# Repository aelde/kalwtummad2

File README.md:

# kalwtummad2
# mini robot

**car robot control over wifi / control over hand using mqtt**\
3d : <https://collaborate.shapr3d.com/v/xkKrqxI_4FUdMemtdK0US>

โปรเจคนี้เกิดจากความสนใจใน esp32 ของผมและพอดีช่วงนั้นอาจารย์มีหุ่นยนต์ดูดฝุ่นราคาถูกที่ไม่ได้ใช้อยู่ตัวนึง และพอดีกับที่ผมมี mpu6050 อยู่ที่บ้านพอดี ผมเลยเกิดไอเดียที่จะสร้างหุ่นยนต์ที่บังคับด้วยการขยับของมือขึ้นมา
เริ่มจากการที่แกะชิ้นส่วนทั้งหมดออกแล้วก็เอาอุปกรณ์ใหม่ใส่เข้าไปแทนหมด แล้วจากนั้นก็เชื่อมอุปกรณ์ทั้งหมดกับ esp32 จนเกิดเป็นหุ่นย์นี้ขึ้นมา(kalwtummad) โดยหุ่นย์นี้จะบังคับด้วยมือผ่าน mqtt และยังสามารถบังคับผ่านหน้า dashboard ได้ด้วย

อุปกรณ์หลักๆใน project
  - esp32
  - mpu6050
  - l298n
  - lcd1602
  - I2C liquid crystal displays

การใช้งาน : หมุนมือไปในทิศที่ต้องการจะให้รถวิ่ง ดูใน HOW_TO_USE.jpeg

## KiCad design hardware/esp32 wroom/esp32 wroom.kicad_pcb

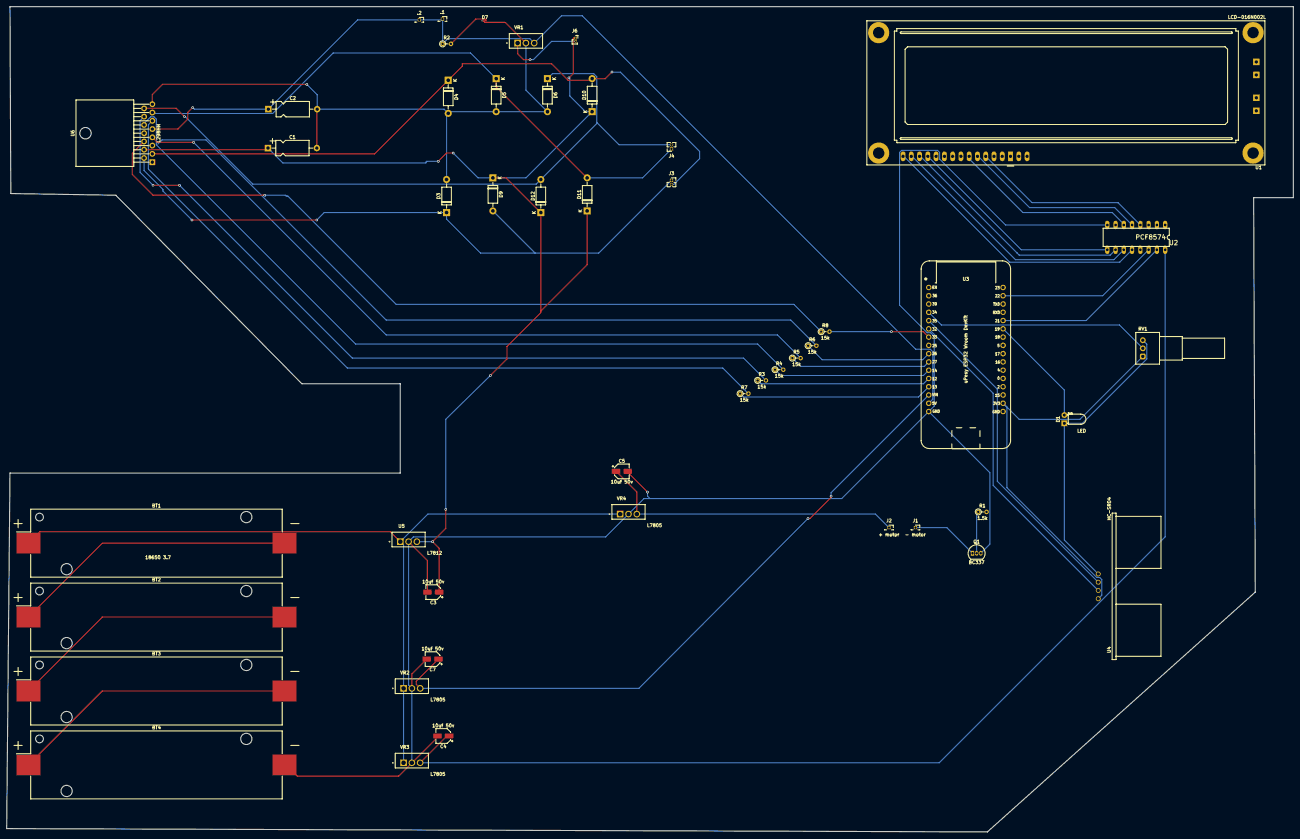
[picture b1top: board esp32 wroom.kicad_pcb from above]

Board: 2 copper layers, 395.2 x 253.5 mm, 47 parts (0 on the bottom side), 47 nets.

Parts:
.1, .2: PinSocket_1x01_P1.27mm_Vertical
BT1, BT2, BT3, BT4: 18650 3.7; BatteryHolder_Keystone_1042_1x18650
C1, C2: 220uf; CP_Axial_L10.0mm_D4.5mm_P15.00mm_Horizontal
C3, C4, C5, C7: 10uf 50v; CP_Elec_4x3.9
D1: LED; LED_D3.0mm_Horizontal_O1.27mm_Z2.0mm
D3, D4, D5, D6, D9, D10, D11, D12: 1N4007; D_DO-41_SOD81_P10.16mm_Horizontal
D7: LED; LED_0201_0603Metric
J1: - motor; PinSocket_1x01_P1.27mm_Vertical
J2: + motor; PinSocket_1x01_P1.27mm_Vertical
J3: motorA; PinSocket_1x02_P1.27mm_Vertical
J4: motorB; PinSocket_1x02_P1.27mm_Vertical
J6: PinSocket_1x02_P1.00mm_Vertical
Q1: BC337; TO-92_Inline
R1: 1.5k; R_Axial_DIN0204_L3.6mm_D1.6mm_P2.54mm_Vertical
R2: 1k; R_Axial_DIN0204_L3.6mm_D1.6mm_P2.54mm_Vertical
R3, R4, R5, R6, R7, R8: 15k; R_Axial_DIN0204_L3.6mm_D1.6mm_P2.54mm_Vertical
RV1: R_Potentiometer; Potentiometer_Alps_RK097_Single_Horizontal
U1: LCD-016N002L
U2: PCF8574; DIL16
U3: uPesy_ESP32_Wroom_DevKit
U4: HC-SR04
U5: L7812; L7805
U6: L298HN; TO-220-15_P2.54x2.54mm_StaggerOdd_Lead5.84mm_TabDown
VR1, VR2, VR3, VR4: L7805

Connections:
5v: .1.1, .2.1, C2.1, R2.1, U3.15 (5V), U6.9 (Vss), VR1.3 (OUTPUT)
/3v3: RV1.1, U3.31 (3V3), U4.1 (VCC)
/5v_control: C7.1, U3.14 (VIN), VR2.3 (OUTPUT)
/5v_lcd: C4.1, U2.16 (VDD), VR3.3 (OUTPUT)
/12v_wheel: C1.1, C3.1, D9.1 (K), D10.1 (K), D11.1 (K), D12.1 (K), J6.1, U5.3 (OUT), U6.4 (Vs)
/D12: R3.1, U3.12 (GPIO12)
/D14: R4.1, U3.11 (GPIO14)
/D18: R1.2, U3.23 (GPIO18)
/D19: D1.2 (A), U3.22 (GPIO19)
/D21: U2.15 (SDA), U3.21 (GPIO21)
/D22: U2.14 (SCL), U3.18 (GPIO22)
/D25: R7.1, U3.13 (GPIO13)
/D26: R6.1, U3.9 (GPIO26)
/D27: R5.1, U3.10 (GPIO27)
/D32: U3.6 (GPIO32), U4.2 (TRIG)
/D33: R8.2, U3.7 (GPIO33)
/D34: RV1.2, U3.4 (GPIO34)
/D35: U3.5 (GPIO35), U4.3 (ECHO)
/GND_1: D1.1 (K), RV1.3, U3.32 (GND), U4.4 (GND)
/dust motor: C5.1, J2.1, VR4.3 (OUTPUT)
Earth: C1.2, C2.2, D3.2 (A), D4.2 (A), D5.2 (A), D6.2 (A), D7.1 (K), U6.1 (SENSE_A), U6.8 (GND), U6.15 (SENSE_B), VR1.2 (GROUND)
GND: BT4.2 (-), C3.2, C4.2, C5.2, C7.2, Q1.3 (E), U2.8 (VSS), U3.16 (GND), U5.2 (GND), VR2.2 (GROUND), VR3.2 (GROUND), VR4.2 (GROUND)
unnamed: BT1.1 (+), U5.1 (IN), VR2.1 (INPUT), VR3.1 (INPUT), VR4.1 (INPUT)
unnamed: BT1.2 (-), BT2.1 (+)
unnamed: BT2.2 (-), BT3.1 (+)
unnamed: BT3.2 (-), BT4.1 (+)
unnamed: D3.1 (K), D9.2 (A), J3.1, U6.2 (OUT1)
unnamed: D7.2 (A), R2.2
unnamed: D4.1 (K), D10.2 (A), J3.2, U6.3 (OUT2)
unnamed: D5.1 (K), D11.2 (A), J4.1, U6.13 (OUT3)
unnamed: D6.1 (K), D12.2 (A), J4.2, U6.14 (OUT4)
unnamed: J1.1, Q1.1 (C)
unnamed: J6.2, VR1.1 (INPUT)
unnamed: Q1.2 (B), R1.1
unnamed: U1.11 (DB4), U2.9 (P4)
unnamed: U1.12 (DB5), U2.10 (P5)
unnamed: U1.13 (DB6), U2.11 (P6)
unnamed: U1.14 (DB7), U2.12 (P7)
unnamed: U1.6 (E), U2.6 (P2)
unnamed: U1.4 (RS), U2.4 (P0)
unnamed: U1.5 (R/~W), U2.5 (P1)
unnamed: R8.1, U6.6 (EnA)
unnamed: R7.2, U6.11 (EnB)
unnamed: R6.2, U6.5 (IN1)
unnamed: R5.2, U6.7 (IN2)
unnamed: R4.2, U6.10 (IN3)
unnamed: R3.2, U6.12 (IN4)
